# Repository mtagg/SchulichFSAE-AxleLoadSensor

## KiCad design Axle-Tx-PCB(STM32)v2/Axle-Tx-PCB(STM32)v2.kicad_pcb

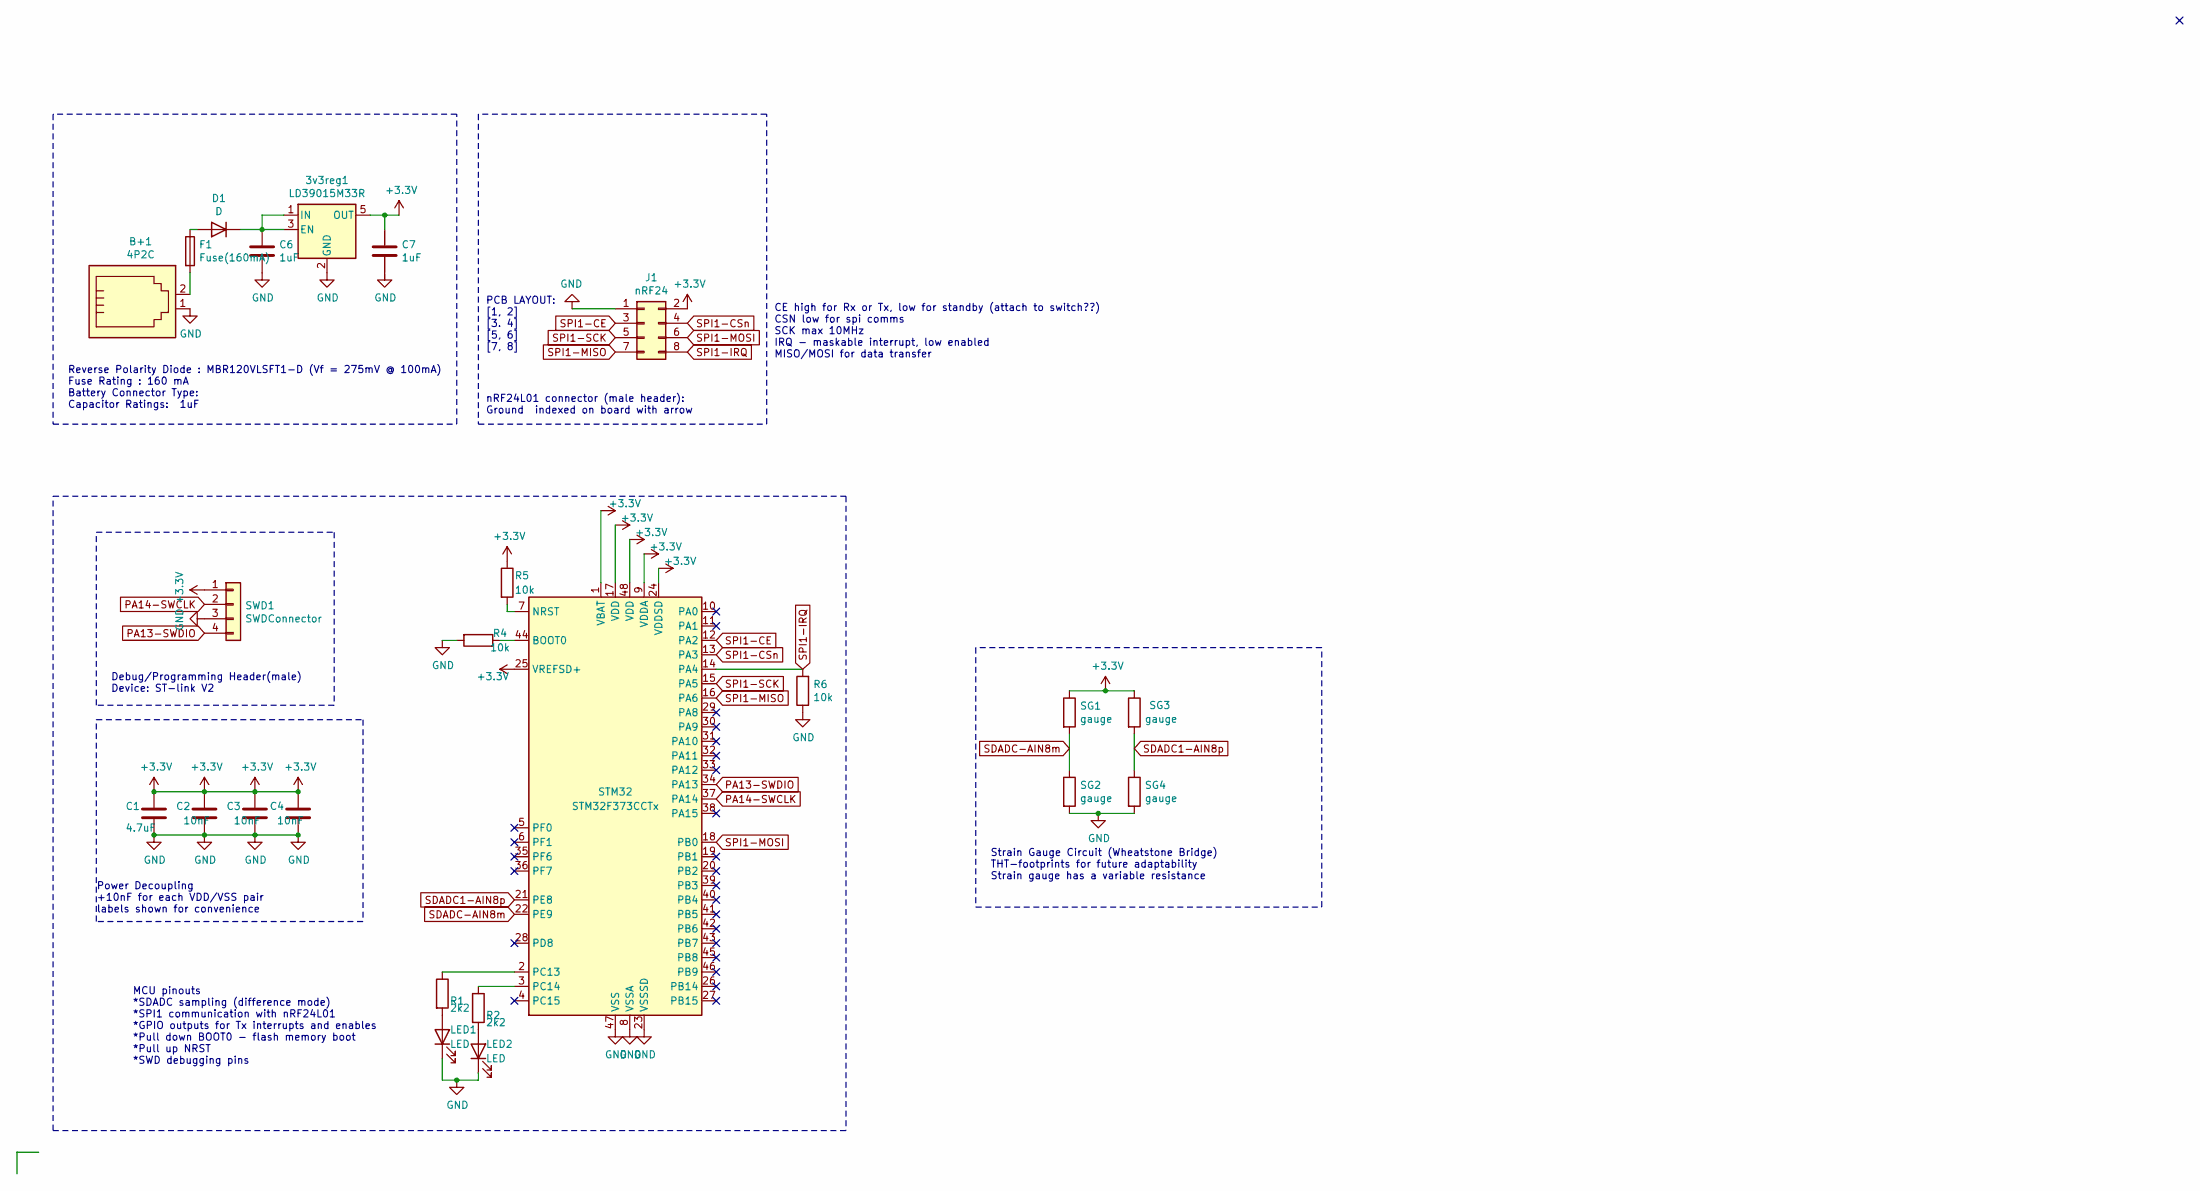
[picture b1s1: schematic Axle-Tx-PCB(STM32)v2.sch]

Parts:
3v3reg1: LD39015M33R; SOT-23-5
B+1: 4P2C; PinSocket_1x02_P2.54mm_Vertical
C1: 4.7uF; C_0805_2012Metric_Pad1.18x1.45mm_HandSolder
C2, C3, C4: 10nF; C_0805_2012Metric_Pad1.18x1.45mm_HandSolder
C6, C7: 1uF; C_0805_2012Metric_Pad1.18x1.45mm_HandSolder
D1: D; D_SOD-123F
F1: Fuse(160mA); Fuse_1206_3216Metric_Pad1.42x1.75mm_HandSolder
J1: nRF24; PinHeader_2x04_P2.54mm_Vertical
LED1, LED2: LED; LED_1206_3216Metric_Pad1.42x1.75mm_HandSolder
R1, R2: 2k2; R_0603_1608Metric_Pad1.05x0.95mm_HandSolder
R4, R5, R6: 10k; R_0603_1608Metric_Pad1.05x0.95mm_HandSolder
SG1, SG2, SG3, SG4: gauge; R_Axial_DIN0204_L3.6mm_D1.6mm_P5.08mm_Horizontal
STM32: STM32F373CCTx; LQFP-48_7x7mm_P0.5mm
SWD1: SWDConnector; PinHeader_1x04_P2.54mm_Vertical

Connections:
+3V3: 3v3reg1.5 (OUT), C1.1, C2.1, C3.1, C4.1, C7.1, J1.2, R5.1, SG1.1, SG3.1, STM32.1 (VBAT), STM32.9 (VDDA), STM32.17 (VDD), STM32.24 (VDDSD), STM32.25 (VREFSD+), STM32.48 (VDD), SWD1.1
GND: 3v3reg1.2 (GND), B+1.1, C1.2, C2.2, C3.2, C4.2, C6.2, C7.2, J1.1, LED1.1 (K), LED2.1 (K), R4.2, R6.1, SG2.2, SG4.2, STM32.8 (VSSA), STM32.23 (VSSSD), STM32.47 (VSS), SWD1.3
unnamed: 3v3reg1.1 (IN), 3v3reg1.3 (EN), C6.1, D1.1 (K)
unnamed: B+1.2, F1.2
unnamed: D1.2 (A), F1.1
unnamed: LED1.2 (A), R1.2
unnamed: LED2.2 (A), R2.2
unnamed: R1.1, STM32.2 (PC13)
unnamed: R2.1, STM32.3 (PC14)
unnamed: R4.1, STM32.44 (BOOT0)
unnamed: R5.2, STM32.7 (NRST)
PA13-SWDIO: STM32.34 (PA13), SWD1.4
PA14-SWCLK: STM32.37 (PA14), SWD1.2
SDADC1-AIN8p: SG3.2, SG4.1, STM32.21 (PE8)
SDADC-AIN8m: SG1.2, SG2.1, STM32.22 (PE9)
SPI1-CE: J1.3, STM32.12 (PA2)
SPI1-CSn: J1.4, STM32.13 (PA3)
SPI1-IRQ: J1.8, R6.2, STM32.14 (PA4)
SPI1-MISO: J1.7, STM32.16 (PA6)
SPI1-MOSI: J1.6, STM32.18 (PB0)
SPI1-SCK: J1.5, STM32.15 (PA5)

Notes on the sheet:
Reverse Polarity Diode : MBR120VLSFT1-D (Vf = 275mV @ 100mA) Fuse Rating : 160 mA Battery Connector Type: Capacitor Ratings: 1uF
Debug/Programming Header(male) Device: ST-link V2
nRF24L01 connector (male header): Ground indexed on board with arrow
Strain Gauge Circuit (Wheatstone Bridge) THT-footprints for future adaptability Strain gauge has a variable resistance
Power Decoupling +10nF for each VDD/VSS pair labels shown for convenience
MCU pinouts *SDADC sampling (difference mode) *SPI1 communication with nRF24L01 *GPIO outputs for Tx interrupts and enables *Pull down BOOT0 - flash memory boot *Pull up NRST *SWD debugging pins
CE high for Rx or Tx, low for standby (attach to switch??) CSN low for spi comms SCK max 10MHz IRQ - maskable interrupt, low enabled MISO/MOSI for data transfer
PCB LAYOUT: [1, 2] [3. 4] [5, 6] [7, 8]

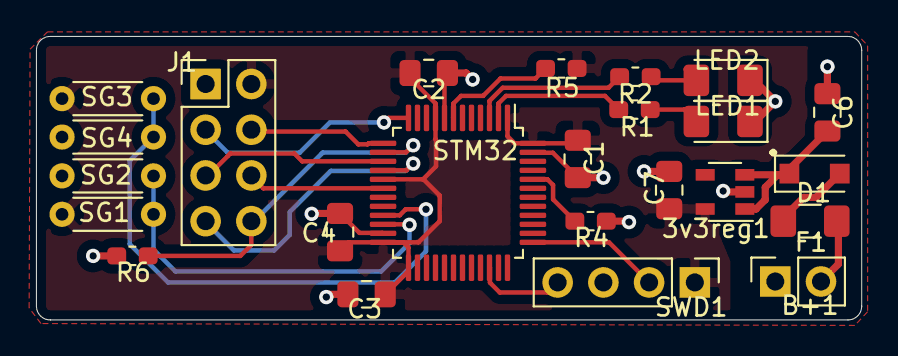
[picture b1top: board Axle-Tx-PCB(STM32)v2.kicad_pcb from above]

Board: 2 copper layers, 45.8 x 15.7 mm, 24 parts (0 on the bottom side), 21 nets.

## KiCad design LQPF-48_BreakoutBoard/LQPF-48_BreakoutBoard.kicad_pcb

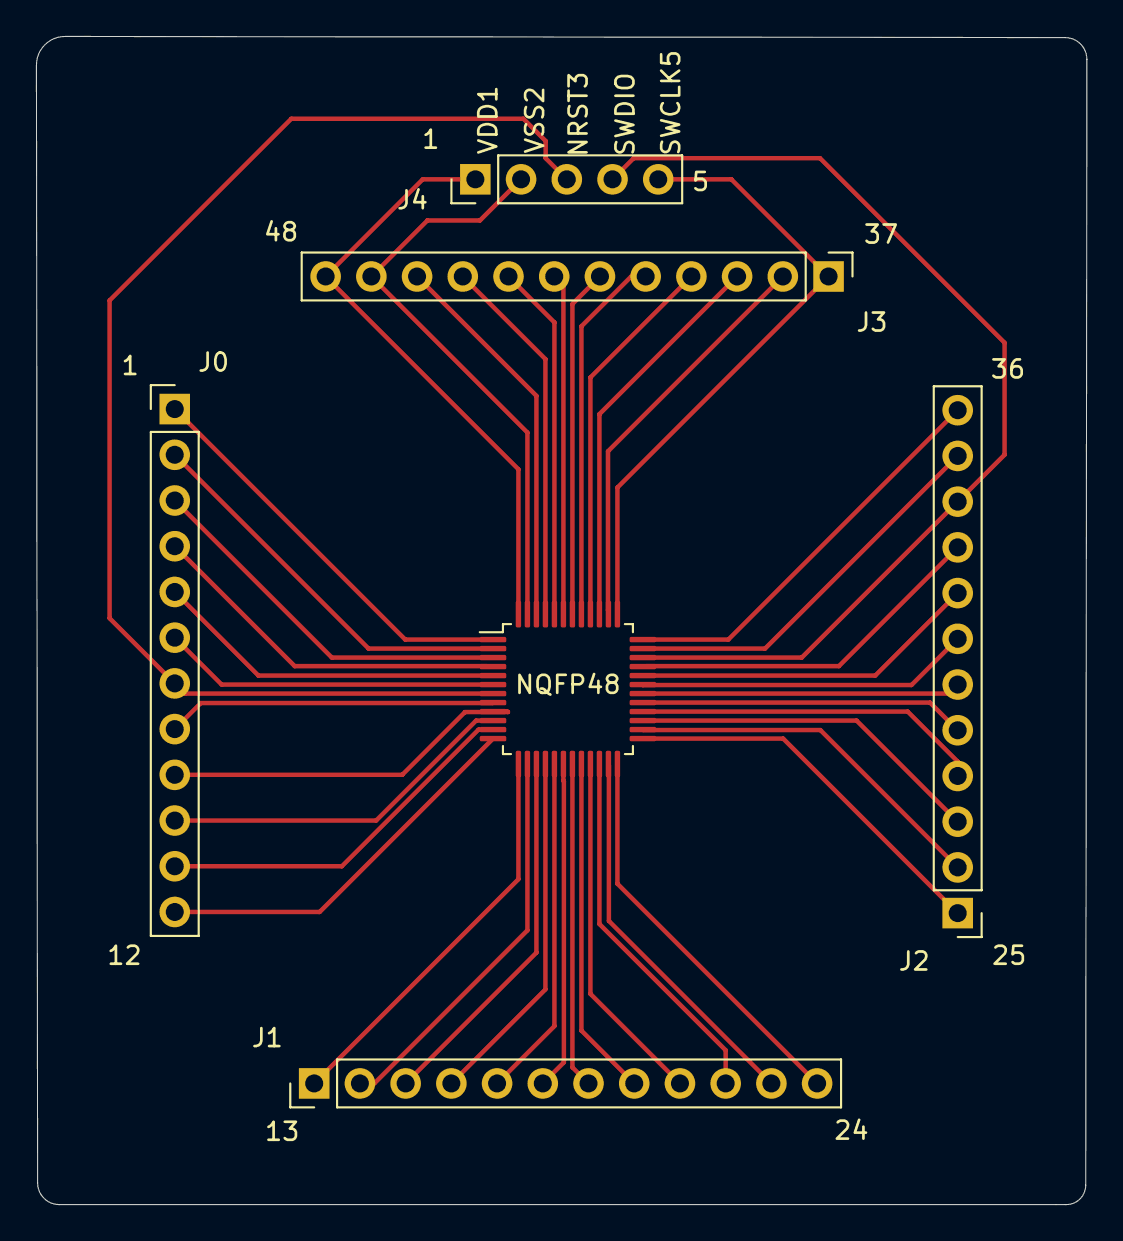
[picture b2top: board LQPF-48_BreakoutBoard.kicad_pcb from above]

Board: 2 copper layers, 58.4 x 64.9 mm, 6 parts (0 on the bottom side), 48 nets.

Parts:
J0, J1, J2, J3: Conn_01x12; PinHeader_1x12_P2.54mm_Vertical
J4: Conn_01x05; PinHeader_1x05_P2.54mm_Vertical
NQFP48: STM32F373CCTx; LQFP-48_7x7mm_P0.5mm

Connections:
BOOT0(44): J3.8, NQFP48.44
NRST(7): J0.7, J4.3, NQFP48.7
PA0(10): J0.10, NQFP48.10
PA1(11): J0.11, NQFP48.11
PA2(12): J0.12, NQFP48.12
PA3(13): J1.1, NQFP48.13
PA4(14): J1.2, NQFP48.14
PA5(15): J1.3, NQFP48.15
PA6(16): J1.4, NQFP48.16
PA8(29): J2.5, NQFP48.29
PA9(30): J2.6, NQFP48.30
PA10(31): J2.7, NQFP48.31
PA11(32): J2.8, NQFP48.32
PA12(33): J2.9, NQFP48.33
PA13(34): J2.10, J4.4, NQFP48.34
PA14(37): J3.1, J4.5, NQFP48.37
PA15(38): J3.2, NQFP48.38
PB0(18): J1.6, NQFP48.18
PB1(19): J1.7, NQFP48.19
PB2(20): J1.8, NQFP48.20
PB3(39): J3.3, NQFP48.39
PB4(40): J3.4, NQFP48.40
PB5(41): J3.5, NQFP48.41
PB6(42): J3.6, NQFP48.42
PB7(43): J3.7, NQFP48.43
PB8(45): J3.9, NQFP48.45
PB9(46): J3.10, NQFP48.46
PB14(26): J2.2, NQFP48.26
PB15(27): J2.3, NQFP48.27
PC13(2): J0.2, NQFP48.2
PC14(3): J0.3, NQFP48.3
PC15(4): J0.4, NQFP48.4
PD8(28): J2.4, NQFP48.28
PE8(21): J1.9, NQFP48.21
PE9(22): J1.10, NQFP48.22
PF0(5): J0.5, NQFP48.5
PF1(6): J0.6, NQFP48.6
PF6(35): J2.11, NQFP48.35
PF7(36): J2.12, NQFP48.36
VBAT(1): J0.1, NQFP48.1
VDD(17): J1.5, NQFP48.17
VDD(48): J3.12, J4.1, NQFP48.48
VDDA(9): J0.9, NQFP48.9
VDDSD(24): J1.12, NQFP48.24
VREFSD+(25): J2.1, NQFP48.25
VSS(47): J3.11, J4.2, NQFP48.47
VSSA(8): J0.8, NQFP48.8
VSSSD(23): J1.11, NQFP48.23

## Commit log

2020-12-19 STM32 adapted PCB designs, preliminary cost planning and finalizing parts list
2020-12-21 first commit with changes to RF module choice, choosing an nRF24L01 board for simplicity and cost, started adjustments to axle-located PCB
2020-12-27 axle-side PCB complete, programming/breakout board complete, midway through recieving-end PCB. parts list has been finalized, ready to order when PCB files have been sent off for manufacturing
2020-12-30 final versions of PCBs, ordered through JLCPCB 2020-12-30
2021-01-25 found and fixed Vss/Vdd short in the reciever PCB, redesigned and optimized capacitors, power circuits, added more general IO, and unused pins for UART, ADC, LEDs which can either be used for debuggi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
2021-02-01 PCB's ready for final review before order
2021-05-09 first version of working transmitter firmware
2021-06-06 Transmitter Firmware debugged, very fast, reliable transmission from both axle sensors, sub 5ms per packet.
